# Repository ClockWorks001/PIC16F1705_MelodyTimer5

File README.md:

# PIC16F1705 Melody Timer Project.
---
This is a simple kitchen/cooking timer by [PIC16F1705][1].
It can choose which of 3 minutes, 5 minutes and 10 minutes.

## Description

This is a simple kitchen/cooking timer by [PIC16F1705][1].
It can choose which of 3 minutes, 5 minutes and 10 minutes.
When it became end of time, it sounds a melody.

I use following peripherals for this Melody Timer project.
  *TMR1* (with interrupt. It makes 1mil second interval.)
  *TMR2*
  *ECCP2*(with TMR2. I use it for PWM output. It buzz a piezo sounder.)
  *GPIO*(input x2 for Switches, output x3 for LED1, LED2, LED3)

Other references.
  You can see in the "PIC16F1705_MelodyTimer5_20150426.ods" file.

## Demo

## Prerequisites

I created this project using the free versions of the following tools:
 * [Microchip MPLAB X][2] (v2.35)
 * [Microchip XC8 Compiler][3] (v1.34)
 * [MPLAB Code Configurator][4] (v2.25. installed as plugin within MPLAB X)
 * [KICAD][6] (BZR4022)

You will need to download and install these tools appropriately before you
can open this project and build it.
I use the [Microchip MPLAB PICkit3 In-Circuit Debugger][5] to program
the chip and debug it.  

## Licence

[MIT](https://github.com/tcnksm/tool/blob/master/LICENCE)

## Author

Hiroshi Murakami  
<https://github.com/ClockWorks001>  

[1]: http://www.microchip.com/wwwproducts/Devices.aspx?dDocName=en538963 "PIC16F1705"
[2]: http://www.microchip.com/pagehandler/en-us/family/mplabx/ "MPLAB X"
[3]: http://www.microchip.com/pagehandler/en_us/devtools/mplabxc/ "MPLAB XC Compilers"
[4]: http://www.microchip.com/pagehandler/en-us/press-release/microchips-free-code-configura.html "MPLAB Code Configurator"
[5]: http://www.microchip.com/Developmenttools/ProductDetails.aspx?PartNO=PG164130 "MPLAB PICkit3 In-Circuit Debugger"
[6]: http://www.kicad-pcb.org/display/KICAD/KiCad+EDA+Software+Suite "KICAD"

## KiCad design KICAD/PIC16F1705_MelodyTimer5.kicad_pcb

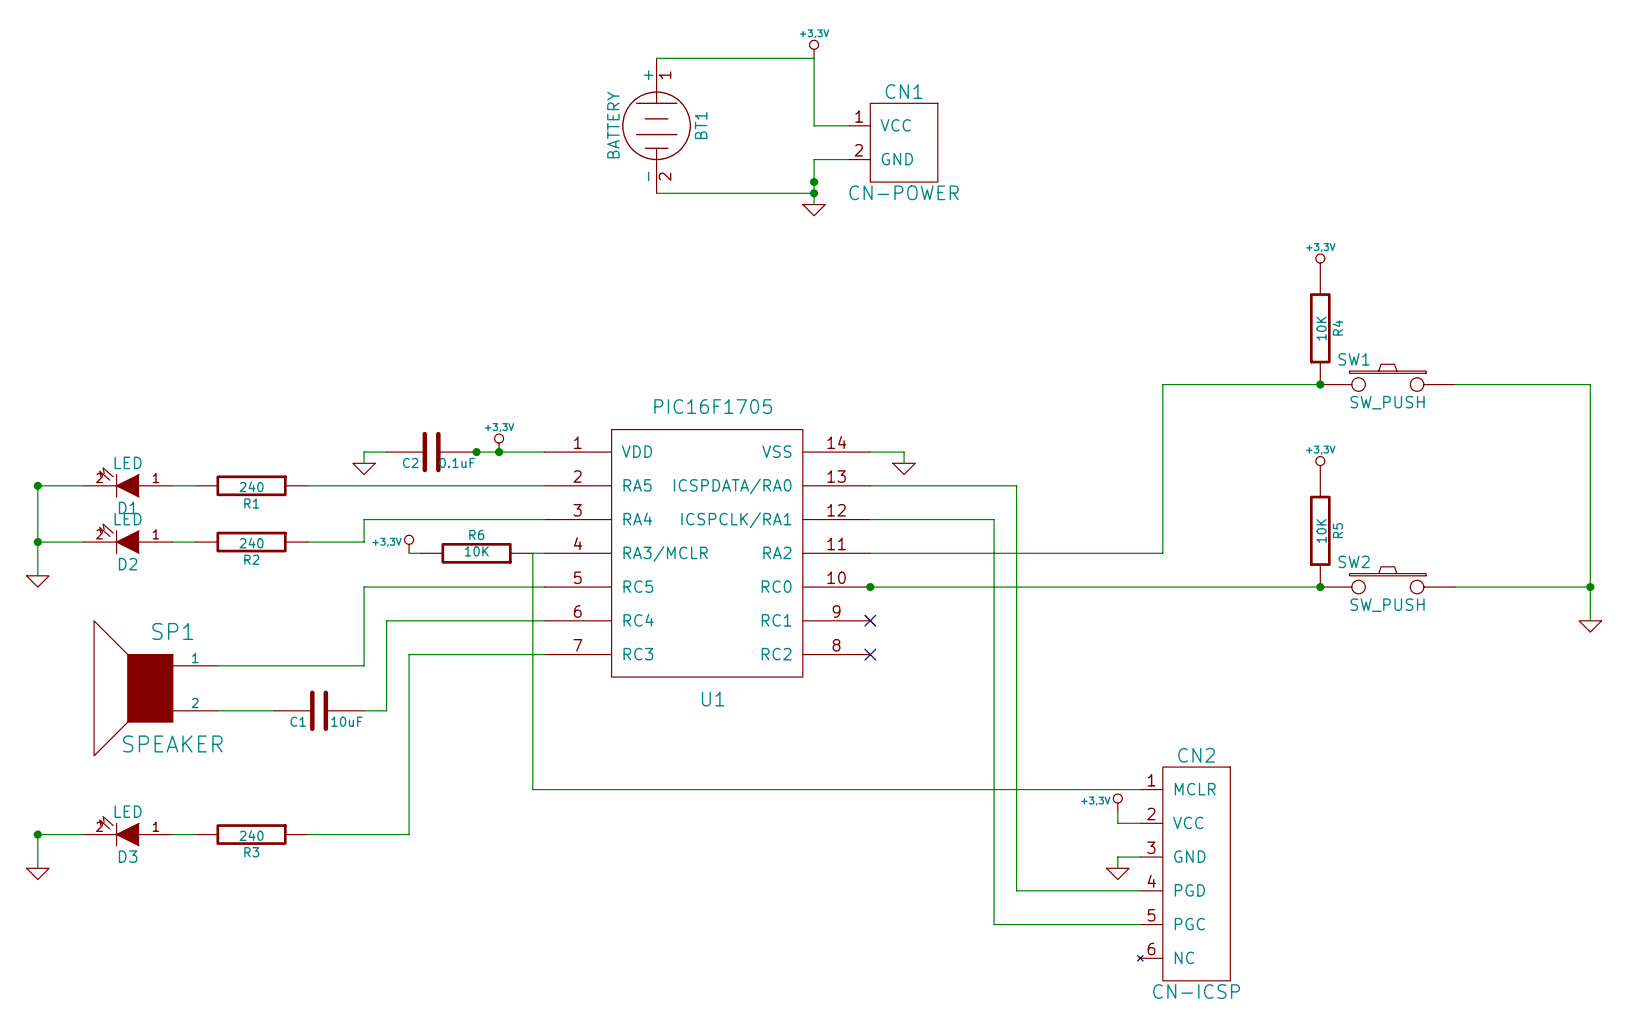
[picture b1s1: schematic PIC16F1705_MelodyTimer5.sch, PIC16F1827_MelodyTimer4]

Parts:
BT1: BATTERY
C1: 10uF
C2: 0.1uF
CN1: CN-POWER
CN2: CN-ICSP
D1, D2, D3: LED
R1, R2, R3: 240
R4, R5, R6: 10K
SP1: SPEAKER
SW1, SW2: SW_PUSH
U1: PIC16F1705

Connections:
+3.3V: BT1.1 (+), C2.2, CN1.1 (VCC), CN2.2 (VCC), R4.2, R5.2, R6.2, U1.1 (VDD)
GND: BT1.2 (-), C2.1, CN1.2 (GND), CN2.3 (GND), D1.2 (K), D2.2 (K), D3.2 (K), SW1.1, SW2.1, U1.14 (VSS)
unnamed: R4.1, SW1.2, U1.11 (RA2)
unnamed: SP1.1, U1.5 (RC5)
unnamed: C1.1, SP1.2
unnamed: C1.2, U1.6 (RC4)
unnamed: R3.1, U1.7 (RC3)
unnamed: R5.1, SW2.2, U1.10 (RC0)
unnamed: CN2.5 (PGC), U1.12 (ICSPCLK/RA1)
unnamed: CN2.4 (PGD), U1.13 (ICSPDATA/RA0)
unnamed: CN2.1 (MCLR), R6.1, U1.4 (RA3/MCLR)
unnamed: R1.1, U1.2 (RA5)
unnamed: D1.1 (A), R1.2
unnamed: R2.1, U1.3 (RA4)
unnamed: D2.1 (A), R2.2
unnamed: D3.1 (A), R3.2

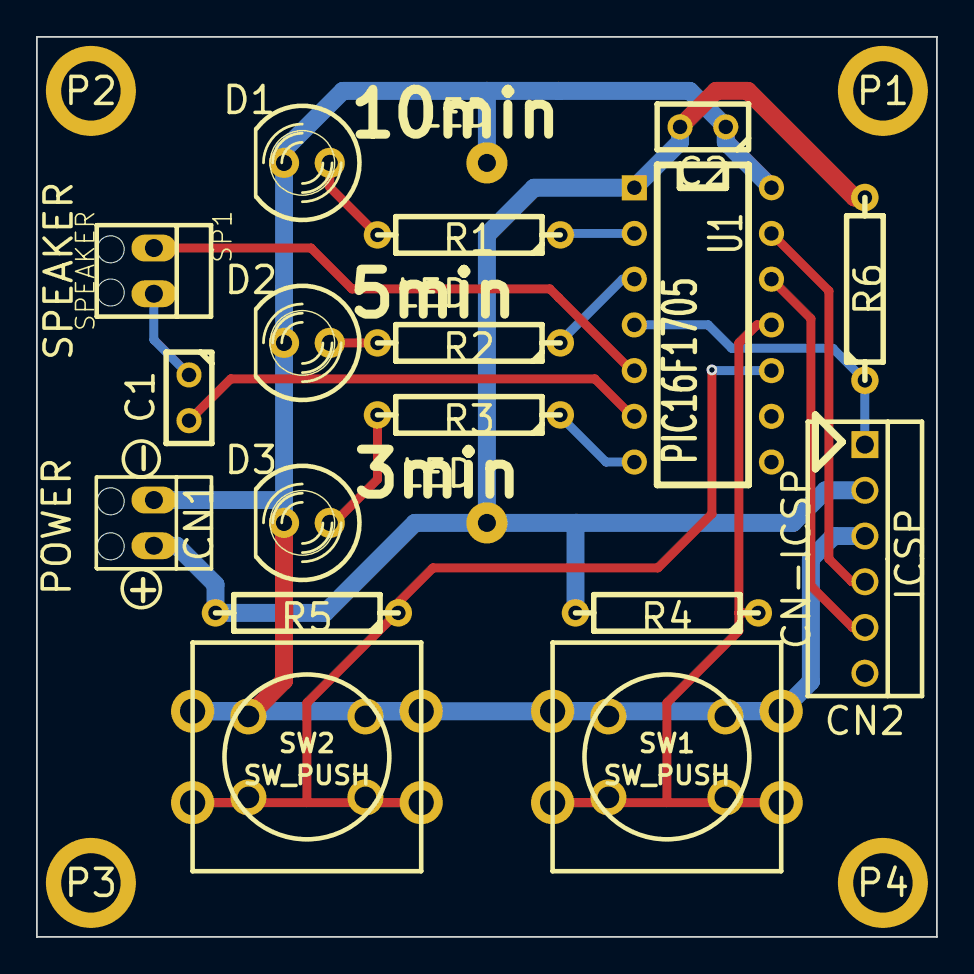
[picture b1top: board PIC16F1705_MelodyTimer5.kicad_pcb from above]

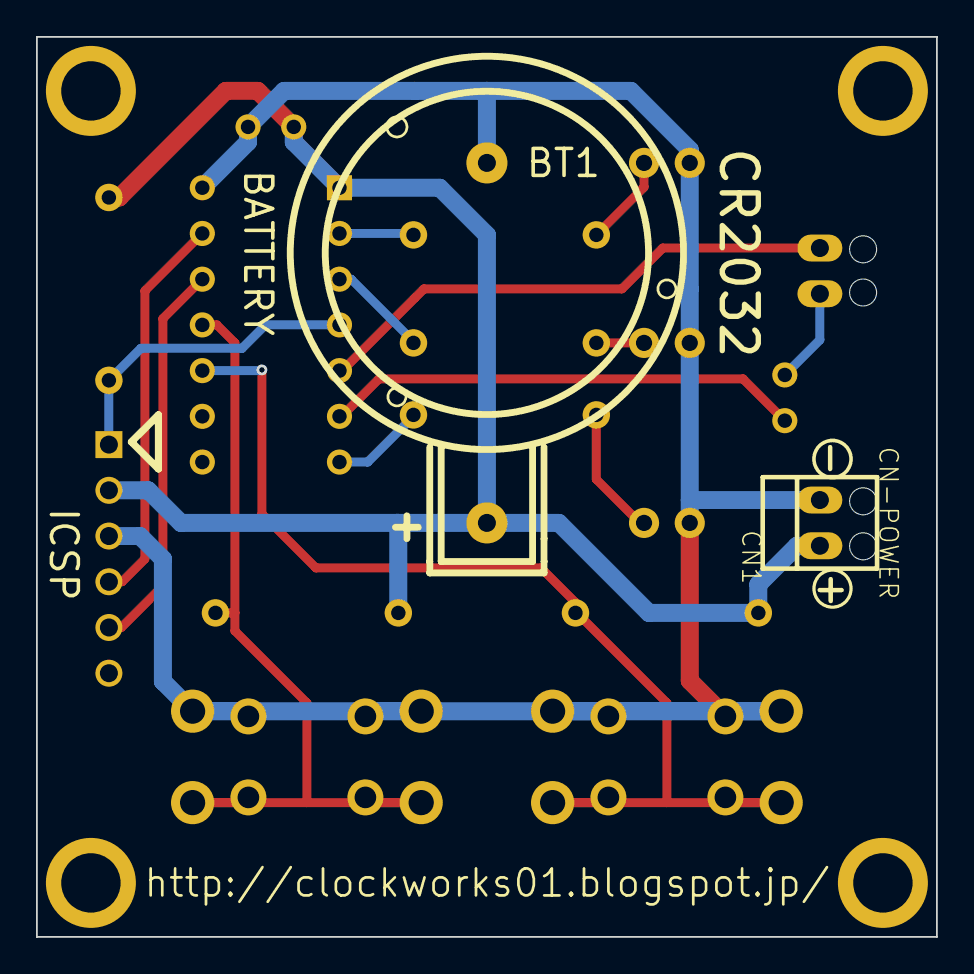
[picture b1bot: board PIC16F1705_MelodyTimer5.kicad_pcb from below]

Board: 2 copper layers, 50.0 x 50.0 mm, 26 parts (2 on the bottom side), 16 nets.

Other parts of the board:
H?: Val**; HOLE1.5mm
H?#2, H?#3, H?#4: Val**; HOLE1.5mm
P1, P2, P3, P4: PAD3mmX5mm

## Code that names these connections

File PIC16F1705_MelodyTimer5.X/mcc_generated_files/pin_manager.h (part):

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// get/set IO_RA0 aliases
#define IO_RA0_TRIS               TRISA0
#define IO_RA0_LAT                LATA0
#define IO_RA0_PORT               RA0
#define IO_RA0_WPU                WPUA0
#define IO_RA0_ANS                ANSA0
#define IO_RA0_SetHigh()    do { LATA0 = 1; } while(0)
#define IO_RA0_SetLow()   do { LATA0 = 0; } while(0)
#define IO_RA0_Toggle()   do { LATA0 = ~LATA0; } while(0)
#define IO_RA0_GetValue()         RA0
#define IO_RA0_SetDigitalInput()    do { TRISA0 = 1; } while(0)
#define IO_RA0_SetDigitalOutput()   do { TRISA0 = 0; } while(0)

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// get/set IO_RA1 aliases
#define IO_RA1_TRIS               TRISA1
#define IO_RA1_LAT                LATA1
#define IO_RA1_PORT               RA1
#define IO_RA1_WPU                WPUA1
#define IO_RA1_ANS                ANSA1
#define IO_RA1_SetHigh()    do { LATA1 = 1; } while(0)
#define IO_RA1_SetLow()   do { LATA1 = 0; } while(0)
#define IO_RA1_Toggle()   do { LATA1 = ~LATA1; } while(0)
#define IO_RA1_GetValue()         RA1
#define IO_RA1_SetDigitalInput()    do { TRISA1 = 1; } while(0)
#define IO_RA1_SetDigitalOutput()   do { TRISA1 = 0; } while(0)

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// get/set IO_RA2 aliases
#define IO_RA2_TRIS               TRISA2
#define IO_RA2_LAT                LATA2
#define IO_RA2_PORT               RA2
#define IO_RA2_WPU                WPUA2
#define IO_RA2_ANS                ANSA2
#define IO_RA2_SetHigh()    do { LATA2 = 1; } while(0)
#define IO_RA2_SetLow()   do { LATA2 = 0; } while(0)
#define IO_RA2_Toggle()   do { LATA2 = ~LATA2; } while(0)
#define IO_RA2_GetValue()         RA2
#define IO_RA2_SetDigitalInput()    do { TRISA2 = 1; } while(0)
#define IO_RA2_SetDigitalOutput()   do { TRISA2 = 0; } while(0)

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#define IO_RA2_SetAnalogMode()   do { ANSA2 = 1; } while(0)
#define IO_RA2_SetDigitalMode()   do { ANSA2 = 0; } while(0)
// get/set IO_RA3 aliases
#define IO_RA3_PORT               RA3
#define IO_RA3_WPU                WPUA3
#define IO_RA3_GetValue()         RA3

#define IO_RA3_SetPullup()    do { WPUA3 = 1; } while(0)
#define IO_RA3_ResetPullup()   do { WPUA3 = 0; } while(0)
// get/set IO_RA4 aliases
#define IO_RA4_TRIS               TRISA4
#define IO_RA4_LAT                LATA4
#define IO_RA4_PORT               RA4
#define IO_RA4_WPU                WPUA4
#define IO_RA4_ANS                ANSA4
#define IO_RA4_SetHigh()    do { LATA4 = 1; } while(0)
#define IO_RA4_SetLow()   do { LATA4 = 0; } while(0)
#define IO_RA4_Toggle()   do { LATA4 = ~LATA4; } while(0)
#define IO_RA4_GetValue()         RA4
#define IO_RA4_SetDigitalInput()    do { TRISA4 = 1; } while(0)
#define IO_RA4_SetDigitalOutput()   do { TRISA4 = 0; } while(0)

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// get/set IO_RA5 aliases
#define IO_RA5_TRIS               TRISA5
#define IO_RA5_LAT                LATA5
#define IO_RA5_PORT               RA5
#define IO_RA5_WPU                WPUA5
#define IO_RA5_SetHigh()    do { LATA5 = 1; } while(0)
#define IO_RA5_SetLow()   do { LATA5 = 0; } while(0)
#define IO_RA5_Toggle()   do { LATA5 = ~LATA5; } while(0)
#define IO_RA5_GetValue()         RA5
#define IO_RA5_SetDigitalInput()    do { TRISA5 = 1; } while(0)
#define IO_RA5_SetDigitalOutput()   do { TRISA5 = 0; } while(0)

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// get/set IO_RC0 aliases
#define IO_RC0_TRIS               TRISC0
#define IO_RC0_LAT                LATC0
#define IO_RC0_PORT               RC0
#define IO_RC0_WPU                WPUC0
#define IO_RC0_ANS                ANSC0
#define IO_RC0_SetHigh()    do { LATC0 = 1; } while(0)
#define IO_RC0_SetLow()   do { LATC0 = 0; } while(0)
#define IO_RC0_Toggle()   do { LATC0 = ~LATC0; } while(0)
#define IO_RC0_GetValue()         RC0
#define IO_RC0_SetDigitalInput()    do { TRISC0 = 1; } while(0)
#define IO_RC0_SetDigitalOutput()   do { TRISC0 = 0; } while(0)

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// get/set IO_RC3 aliases
#define IO_RC3_TRIS               TRISC3
#define IO_RC3_LAT                LATC3
#define IO_RC3_PORT               RC3
#define IO_RC3_WPU                WPUC3
#define IO_RC3_ANS                ANSC3
#define IO_RC3_SetHigh()    do { LATC3 = 1; } while(0)
#define IO_RC3_SetLow()   do { LATC3 = 0; } while(0)
#define IO_RC3_Toggle()   do { LATC3 = ~LATC3; } while(0)
#define IO_RC3_GetValue()         RC3
#define IO_RC3_SetDigitalInput()    do { TRISC3 = 1; } while(0)
#define IO_RC3_SetDigitalOutput()   do { TRISC3 = 0; } while(0)

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// get/set COG1B aliases
#define COG1B_TRIS               TRISC4
#define COG1B_LAT                LATC4
#define COG1B_PORT               RC4
#define COG1B_WPU                WPUC4
#define COG1B_ANS                ANSC4
#define COG1B_SetHigh()    do { LATC4 = 1; } while(0)
#define COG1B_SetLow()   do { LATC4 = 0; } while(0)
#define COG1B_Toggle()   do { LATC4 = ~LATC4; } while(0)
#define COG1B_GetValue()         RC4
#define COG1B_SetDigitalInput()    do { TRISC4 = 1; } while(0)
#define COG1B_SetDigitalOutput()   do { TRISC4 = 0; } while(0)

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// get/set COG1A aliases
#define COG1A_TRIS               TRISC5
#define COG1A_LAT                LATC5
#define COG1A_PORT               RC5
#define COG1A_WPU                WPUC5
#define COG1A_ANS                ANSC5
#define COG1A_SetHigh()    do { LATC5 = 1; } while(0)
#define COG1A_SetLow()   do { LATC5 = 0; } while(0)
#define COG1A_Toggle()   do { LATC5 = ~LATC5; } while(0)
#define COG1A_GetValue()         RC5
#define COG1A_SetDigitalInput()    do { TRISC5 = 1; } while(0)
#define COG1A_SetDigitalOutput()   do { TRISC5 = 0; } while(0)

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
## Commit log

2015-07-22 updated a DEMO gif animation

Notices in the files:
PIC16F1705_MelodyTimer5.X/mcc_generated_files/pin_manager.h:
Copyright (c) 2013 - 2015 released Microchip Technology Inc.  All rights reserved.
